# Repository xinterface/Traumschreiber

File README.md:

# Traumschreiber
Repository of the Traumschreiber and all affiliated projects and theses

## Thus far, this includes:

- A collection of theses
- The repos of the two projects concerned with App Design for the Traumschreiber. More information [on EEGDroid](https://github.com/neuroinfo-os/Traumschreiber/blob/master/Theses/App%20Development/RojasCampos_AppRecordStoreManageEEG.pdf) and on [Traumschreiber mobile EEG](https://github.com/neuroinfo-os/Traumschreiber/blob/master/Theses/Event%20Related%20Potentials/Vidal_AuditoryEvokedPotentials.pdf)
- A collection of operation manuals of the hardware components
- In Progress: Streaming implementation
- In Progress: Embedded System and BLE
# Traumschreiber's List (Version 2.8) + (Version EEG_v2_92_X25)
https://docs.google.com/spreadsheets/d/1prQXEEBJC7Lh-TTywT1AkwJn4IeFenbX4uT630RnToc/edit#gid=0

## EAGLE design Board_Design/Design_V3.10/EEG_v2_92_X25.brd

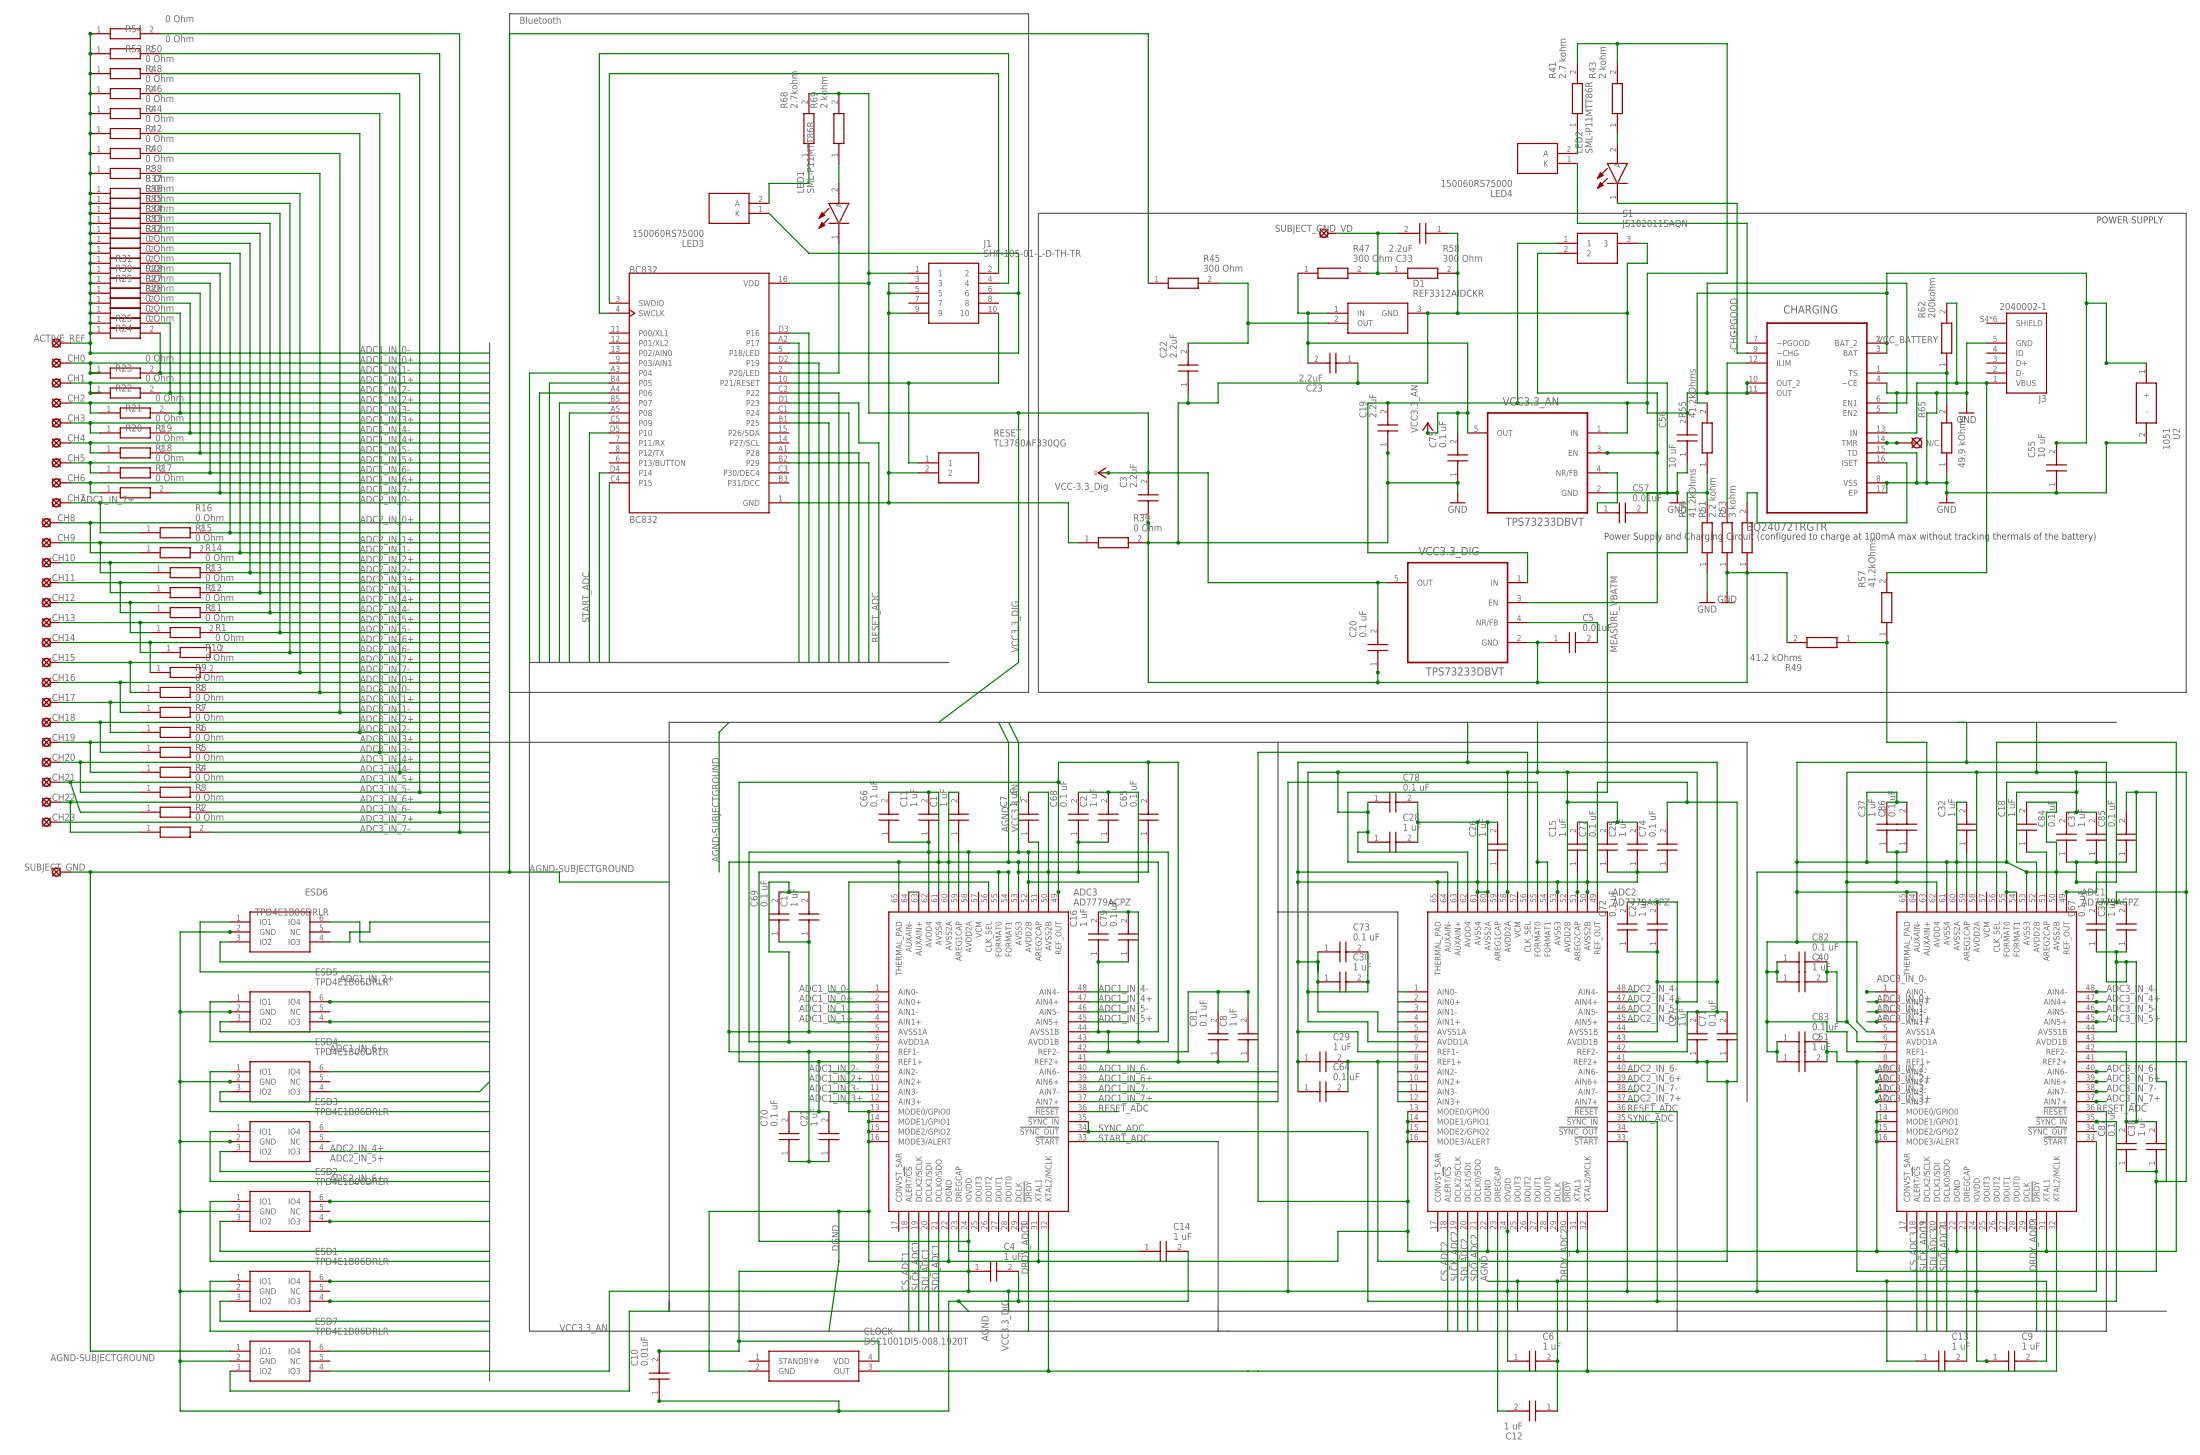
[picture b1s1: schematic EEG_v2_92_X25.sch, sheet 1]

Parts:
ACTIVE_REF: SE11
ADC1, ADC2, ADC3: AD7779ACPZ; QFN50P900X900X80-65N
BC832: BC832; XCVR_BC832
C1, C2, C4, C6, C7, C8, C9, C11, C12, C13, C14, C15, C16, C17, C18, C21, C24, C25, C26, C27, C28, C29, C30, C31, C32, C37, C38, C39, C40, C51: 1 uF; CAPC1005X33N
C3, C19, C22, C23, C33: 2.2uF; CAPC0603X33N
C5, C10, C57: 0.01uF; CAPC0603X33N
C20, C64, C65, C66, C67, C68, C69, C70, C71, C72, C73, C74, C75, C77, C78, C79, C81, C82, C83, C84, C85, C86, C87: 0.1 uF; CAPC0603X33N
C55, C56: 10 uF; CAPC1608X100N
CH0, CH1, CH2, CH3, CH4, CH5, CH6, CH7, CH8, CH9, CH10, CH11, CH12, CH13, CH14, CH15, CH16, CH17, CH18, CH19, CH20, CH21, CH22, CH23: SE11
CHARGING: BQ24072TRGTR; QFN50P300X300X100-17N
CLOCK: DSC1001DI5-008.1920T; DSC1001DI50081920T
D1: REF3312AIDCKR; SOT65P210X110-3N
ESD1, ESD2, ESD3, ESD4, ESD5, ESD6, ESD7: TPD4E1B06DRLR; SOP50P160X60-6N
J1: SHF-105-01-L-D-TH-TR; SHF10501LDTHTR
J3: 2040002-1; TE_2040002-1
LED1, LED2: SML-P11MTT86R; LEDC1006X25N
LED3, LED4: 150060RS75000; LEDC1608X80N
R1, R2, R3, R4, R5, R6, R7, R8, R9, R10, R11, R12, R13, R14, R15, R16, R17, R18, R19, R20, R21, R22, R23, R24, R25, R26, R27, R28, R29, R30, R31, R32, R33, R34, R35, R36, R37, R38, R39, R40, R42, R44, R46, R48, R50, R52, R54: 0 Ohm; RESC1608X55N
R41: 2.7 kohm; RESC0603X26N
R43, R69: 2 kohm; RESC0603X26N
R45, R47, R58: 300 Ohm; RESC0603X26N
R49: 41.2 kOhms; RESC0603X28N
R51: 2.2 kohm; RESC0603X28N
R53: 3 kohm; RESC0603X26N
R55, R56, R57: 41.2kOhms; RESC0603X28N
R62: 200kohm; RESC0603X28N
R65: 49.9 kOhms; RESC0603X28N
R68: 2.7kohm; RESC0603X26N
RESET: TL3780AF330QG
S1: JS102011SAQN
SUBJECT_GND: SE11
SUBJECT_GND_VD: SE11
U2: 1051
VCC3.3_AN, VCC3.3_DIG: TPS73233DBVT; SOT95P280X145-5N

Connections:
-CHG: CHARGING.9 (~CHG), LED2.1 (K)
-PGOOD: CHARGING.7 (~PGOOD), LED4.1 (K)
ADC1_IN_0+: ADC3.2 (AIN0+), CH0.MP, ESD6.4 (IO3), R23.1
ADC1_IN_0-: ACTIVE_REF.MP, ADC3.1 (AIN0-), ESD6.6 (IO4), R24.1, R25.1, R26.1, R27.1, R28.1, R29.1, R30.1, R31.1, R32.1, R33.1, R34.1, R35.1, R36.1, R37.1, R38.1, R40.1, R42.1, R44.1, R46.1, R48.1, R50.1, R52.1, R54.1
ADC1_IN_1+: ADC3.4 (AIN1+), CH1.MP, ESD6.3 (IO2), R22.1
ADC1_IN_1-: ADC3.3 (AIN1-), R23.2, R24.2
ADC1_IN_2+: ADC3.10 (AIN2+), CH2.MP, ESD6.1 (IO1), R21.1
ADC1_IN_2-: ADC3.9 (AIN2-), R22.2, R25.2
ADC1_IN_3+: ADC3.12 (AIN3+), CH3.MP, ESD5.6 (IO4), R20.1
ADC1_IN_3-: ADC3.11 (AIN3-), R21.2, R26.2
ADC1_IN_4+: ADC3.47 (AIN4+), CH4.MP, ESD5.4 (IO3), R19.1
ADC1_IN_4-: ADC3.48 (AIN4-), R20.2, R27.2
ADC1_IN_5+: ADC3.45 (AIN5+), CH5.MP, ESD5.3 (IO2), R18.1
ADC1_IN_5-: ADC3.46 (AIN5-), R19.2, R28.2
ADC1_IN_6+: ADC3.39 (AIN6+), CH6.MP, ESD5.1 (IO1), R17.1
ADC1_IN_6-: ADC3.40 (AIN6-), R18.2, R29.2
ADC1_IN_7+: ADC3.37 (AIN7+), CH7.MP, ESD4.6 (IO4), R16.1
ADC1_IN_7-: ADC3.38 (AIN7-), R17.2, R30.2
ADC2_IN_0+: ADC2.2 (AIN0+), CH8.MP, ESD4.4 (IO3), R15.1
ADC2_IN_0-: ADC2.1 (AIN0-), R16.2, R31.2
ADC2_IN_1+: ADC2.4 (AIN1+), CH9.MP, ESD4.3 (IO2), R14.1
ADC2_IN_1-: ADC2.3 (AIN1-), R15.2, R32.2
ADC2_IN_2+: ADC2.10 (AIN2+), CH10.MP, ESD4.1 (IO1), R13.1
ADC2_IN_2-: ADC2.9 (AIN2-), R14.2, R33.2
ADC2_IN_3+: ADC2.12 (AIN3+), CH11.MP, ESD3.6 (IO4), R12.1
ADC2_IN_3-: ADC2.11 (AIN3-), R13.2, R34.2
ADC2_IN_4+: ADC2.47 (AIN4+), CH12.MP, ESD3.4 (IO3), R11.1
ADC2_IN_4-: ADC2.48 (AIN4-), R12.2, R35.2
ADC2_IN_5+: ADC2.45 (AIN5+), CH13.MP, ESD3.3 (IO2), R1.1
ADC2_IN_5-: ADC2.46 (AIN5-), R11.2, R36.2
ADC2_IN_6+: ADC2.39 (AIN6+), CH14.MP, ESD3.1 (IO1), R10.1
ADC2_IN_6-: ADC2.40 (AIN6-), R1.2, R37.2
ADC2_IN_7+: ADC2.37 (AIN7+), CH15.MP, ESD2.6 (IO4), R9.1
ADC2_IN_7-: ADC2.38 (AIN7-), R10.2, R38.2
ADC3_IN_0+: ADC1.2 (AIN0+), CH16.MP, ESD2.4 (IO3), R8.1
ADC3_IN_0-: ADC1.1 (AIN0-), R9.2, R40.2
ADC3_IN_1+: ADC1.4 (AIN1+), CH17.MP, ESD2.3 (IO2), R7.1
ADC3_IN_1-: ADC1.3 (AIN1-), R8.2, R42.2
ADC3_IN_2+: ADC1.10 (AIN2+), CH18.MP, ESD2.1 (IO1), R6.1
ADC3_IN_2-: ADC1.9 (AIN2-), R7.2, R44.2
ADC3_IN_3+: ADC1.12 (AIN3+), CH19.MP, ESD1.6 (IO4), R5.1
ADC3_IN_3-: ADC1.11 (AIN3-), R6.2, R46.2
ADC3_IN_4+: ADC1.47 (AIN4+), CH20.MP, ESD1.4 (IO3), R4.1
ADC3_IN_4-: ADC1.48 (AIN4-), R5.2, R48.2
ADC3_IN_5+: ADC1.45 (AIN5+), CH21.MP, ESD1.3 (IO2), R3.1
ADC3_IN_5-: ADC1.46 (AIN5-), R4.2, R50.2
ADC3_IN_6+: ADC1.39 (AIN6+), CH22.MP, ESD1.1 (IO1), R2.1
ADC3_IN_6-: ADC1.40 (AIN6-), R3.2, R52.2
ADC3_IN_7+: ADC1.37 (AIN7+), CH23.MP, ESD7.6 (IO4)
ADC3_IN_7-: ADC1.38 (AIN7-), R2.2, R54.2
AGND: ADC1.5 (AVSS1A), ADC1.7 (REF1-), ADC1.42 (REF2-), ADC1.44 (AVSS1B), ADC1.50 (AVSS2B), ADC1.53 (AVSS3), ADC1.60 (AVSS2A), ADC1.61 (AVSS4), ADC1.64 (AUXAIN-), ADC1.65 (THERMAL_PAD), ADC2.5 (AVSS1A), ADC2.7 (REF1-), ADC2.42 (REF2-), ADC2.44 (AVSS1B), ADC2.50 (AVSS2B), ADC2.53 (AVSS3), ADC2.60 (AVSS2A), ADC2.61 (AVSS4), ADC2.64 (AUXAIN-), ADC2.65 (THERMAL_PAD), ADC3.5 (AVSS1A), ADC3.7 (REF1-), ADC3.42 (REF2-), ADC3.44 (AVSS1B), ADC3.50 (AVSS2B), ADC3.53 (AVSS3), ADC3.60 (AVSS2A), ADC3.61 (AVSS4), ADC3.65 (THERMAL_PAD), C1.2, C2.1, C3.1, C4.2, C5.1, C6.2, C7.2, C8.2, C9.2, C10.1, C11.2, C12.1, C13.1, C14.2, C15.2, C16.1, C17.1, C18.2, C19.1, C20.1, C21.1, C22.1, C23.1, C24.1, C25.1, C26.2, C27.2, C28.2, C29.1, C30.1, C31.1, C32.2, C33.1, C37.2, C38.2, C39.1, C40.1, C51.1, C55.1, C56.1, C57.2, C64.1, C65.1, C66.2, C67.1, C68.1, C69.1, C70.1, C71.2, C72.1, C73.1, C74.1, C75.1, C77.1, C78.2, C79.1, C81.2, C82.1, C83.1, C84.1, C85.1, C86.2, C87.2, CHARGING.4 (~CE), CHARGING.5 (EN2), CHARGING.8 (VSS), CHARGING.15 (TD), CHARGING.17 (EP), D1.3 (GND), ESD1.2 (GND), ESD2.2 (GND), ESD3.2 (GND), ESD4.2 (GND), ESD5.2 (GND), ESD6.2 (GND), ESD7.2 (GND), J3.5 (GND), R39.2, R49.2, R51.1, R53.1, R56.1, R58.2, R65.1, S1.3, U2.2 (-), VCC3.3_AN.2 (GND), VCC3.3_DIG.2 (GND)
AGND-SUBJECTGROUND: ESD7.1 (IO1), R45.1, SUBJECT_GND.MP
CS_ADC1: ADC3.18 (ALERT/!CS), BC832.A4 (P06)
CS_ADC2: ADC2.18 (ALERT/!CS), BC832.A5 (P08)
CS_ADC3: ADC1.18 (ALERT/!CS), BC832.C1 (P24)
DGND: ADC1.13 (MODE0/GPIO0), ADC1.14 (MODE1/GPIO1), ADC1.15 (MODE2/GPIO2), ADC1.16 (MODE3/ALERT), ADC1.22 (DGND), ADC1.31 (XTAL1), ADC1.56 (CLK_SEL), ADC2.13 (MODE0/GPIO0), ADC2.14 (MODE1/GPIO1), ADC2.15 (MODE2/GPIO2), ADC2.16 (MODE3/ALERT), ADC2.22 (DGND), ADC2.31 (XTAL1), ADC2.56 (CLK_SEL), ADC3.13 (MODE0/GPIO0), ADC3.14 (MODE1/GPIO1), ADC3.15 (MODE2/GPIO2), ADC3.16 (MODE3/ALERT), ADC3.22 (DGND), ADC3.31 (XTAL1), ADC3.56 (CLK_SEL), BC832.1 (GND), CLOCK.2 (GND), J1.3, J1.5, J1.9, R39.1, RESET.2
DRDY_ADC1: ADC3.30 (!DRDY), BC832.A2 (P17)
DRDY_ADC2: ADC2.30 (!DRDY), BC832.D4 (P14)
DRDY_ADC3: ADC1.30 (!DRDY), BC832.B1 (P25)
MEASURE_VBATM: ADC2.63 (AUXAIN+), R55.1, R56.2
MEASURE_VUSB: ADC1.63 (AUXAIN+), R49.1, R57.1
unnamed: ADC3.59 (AREG1CAP), C1.1
unnamed: ADC2.23 (DREGCAP), C12.2
unnamed: C22.2, D1.2 (OUT), R45.2
unnamed: C5.2, VCC3.3_DIG.4 (NR/FB)
unnamed: BC832.2 (P20/LED), LED1.1 (K)
unnamed: ADC3.63 (AUXAIN+), ADC3.64 (AUXAIN-)
unnamed: ADC3.51 (AREG2CAP), C7.1
unnamed: LED3.2 (A), R68.1
unnamed: LED1.2 (A), R69.1
unnamed: LED4.2 (A), R41.1
unnamed: ADC2.51 (AREG2CAP), C15.1
unnamed: ADC3.23 (DREGCAP), C14.1
unnamed: ADC1.23 (DREGCAP), C13.2
unnamed: LED2.2 (A), R43.1
unnamed: C57.1, VCC3.3_AN.4 (NR/FB)
unnamed: ADC1.59 (AREG1CAP), C32.1
unnamed: ADC2.59 (AREG1CAP), C26.1
unnamed: ADC1.51 (AREG2CAP), C18.1
unnamed: CHARGING.1 (TS), R62.1, R65.2
unnamed: CHARGING.16 (ISET), R53.2
unnamed: CHARGING.12 (ILIM), R51.2
P18/LED: BC832.5 (P18/LED), J1.6, LED3.1 (K)
POWERUP: S1.2, VCC3.3_AN.3 (EN), VCC3.3_DIG.3 (EN)
REF_ADC1: ADC3.8 (REF1+), ADC3.41 (REF2+), ADC3.49 (REF_OUT), C8.1, C21.2, C65.2, C70.2, C81.1
REF_ADC2: ADC2.8 (REF1+), ADC2.41 (REF2+), ADC2.49 (REF_OUT), C27.1, C29.2, C64.2, C71.1, C74.2
REF_ADC3: ADC1.8 (REF1+), ADC1.41 (REF2+), ADC1.49 (REF_OUT), C38.1, C51.2, C83.2, C85.2, C87.1
RESET: BC832.10 (P21/RESET), J1.10, RESET.1
RESET_ADC: ADC1.36 (!RESET), ADC2.36 (!RESET), ADC3.36 (!RESET), BC832.D1 (P23)
SDCLK: BC832.4 (SWCLK), J1.4
SDIO: BC832.3 (SWDIO), J1.2
SDI_ADC1: ADC3.20 (DCLK1/SDI), BC832.C4 (P15)
SDI_ADC2: ADC2.20 (DCLK1/SDI), BC832.B5 (P07)
SDI_ADC3: ADC1.20 (DCLK1/SDI), BC832.A1 (P28)
SDO_ADC1: ADC3.21 (DCLK0/SDO), BC832.D3 (P16)
SDO_ADC2: ADC2.21 (DCLK0/SDO), BC832.B4 (P05)
SDO_ADC3: ADC1.21 (DCLK0/SDO), BC832.B2 (P29)
SHIELD: J3.S4 (SHIELD), J3.S5 (SHIELD), J3.SH1 (SHIELD), J3.SH2 (SHIELD), J3.SH3 (SHIELD), J3.SH4 (SHIELD)
SLCK_ADC1: ADC3.19 (DCLK2/SCLK), BC832.A3 (P04)
SLCK_ADC2: ADC2.19 (DCLK2/SCLK), BC832.D2 (P19)
SLCK_ADC3: ADC1.19 (DCLK2/SCLK), BC832.C2 (P22)
START_ADC: ADC3.33 (!START), BC832.D5 (P10)
SYNC_ADC: ADC1.35 (!SYNC_IN), ADC2.35 (!SYNC_IN), ADC3.34 (!SYNC_OUT), ADC3.35 (!SYNC_IN)
USB_5VOLT+: CHARGING.13 (IN), J3.1 (VBUS), R57.2, R62.2
VCC3.3_AN: ADC1.6 (AVDD1A), ADC1.43 (AVDD1B), ADC1.52 (AVDD2B), ADC1.58 (AVDD2A), ADC1.62 (AVDD4), ADC2.6 (AVDD1A), ADC2.43 (AVDD1B), ADC2.52 (AVDD2B), ADC2.58 (AVDD2A), ADC2.62 (AVDD4), ADC3.6 (AVDD1A), ADC3.43 (AVDD1B), ADC3.52 (AVDD2B), ADC3.58 (AVDD2A), ADC3.62 (AVDD4), C2.2, C11.1, C16.2, C17.2, C23.2, C24.2, C25.2, C28.1, C30.2, C31.2, C37.1, C39.2, C40.2, C66.1, C67.2, C68.2, C69.2, C72.2, C73.2, C75.2, C77.2, C78.1, C79.2, C82.2, C84.2, C86.1, D1.1 (IN), ESD7.3 (IO2), R47.1, VCC3.3_AN.5 (OUT)
VCC3.3_DIG: ADC1.24 (IOVDD), ADC1.33 (!START), ADC1.54 (FORMAT1), ADC1.55 (FORMAT0), ADC2.24 (IOVDD), ADC2.33 (!START), ADC2.54 (FORMAT1), ADC2.55 (FORMAT0), ADC3.24 (IOVDD), ADC3.54 (FORMAT1), ADC3.55 (FORMAT0), BC832.16 (VDD), C3.2, C4.1, C6.1, C9.1, C10.2, C20.2, CLOCK.4 (VDD), ESD7.4 (IO3), J1.1, R68.2, R69.2, VCC3.3_DIG.5 (OUT)
VCC_BATTERY: C55.2, CHARGING.2 (BAT_2), CHARGING.3 (BAT), R55.2, U2.1 (+)
VIRTUAL_GND_PASSIVE: C33.2, R47.2, R58.1, SUBJECT_GND_VD.MP
V_OUT_CHARGER: C19.2, C56.2, CHARGING.6 (EN1), CHARGING.10 (OUT_2), CHARGING.11 (OUT), R41.2, R43.2, S1.1, VCC3.3_AN.1 (IN), VCC3.3_DIG.1 (IN)
XTAL_OUT: ADC1.32 (XTAL2/MCLK), ADC2.32 (XTAL2/MCLK), ADC3.32 (XTAL2/MCLK), CLOCK.3 (OUT)

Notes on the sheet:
Power Supply and Charging Circuit (configured to charge at 100mA max without tracking thermals of the battery)
POWER SUPPLY
Bluetooth

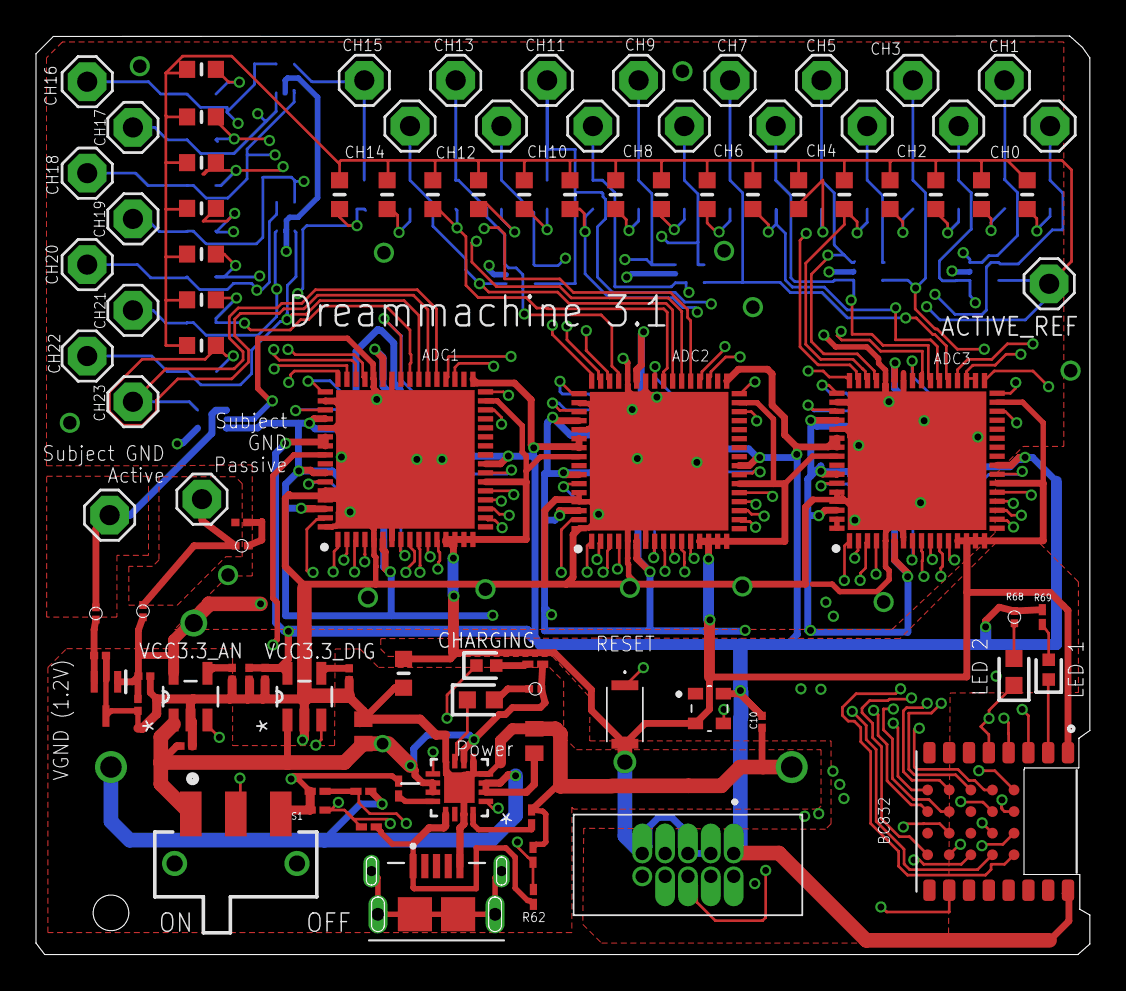
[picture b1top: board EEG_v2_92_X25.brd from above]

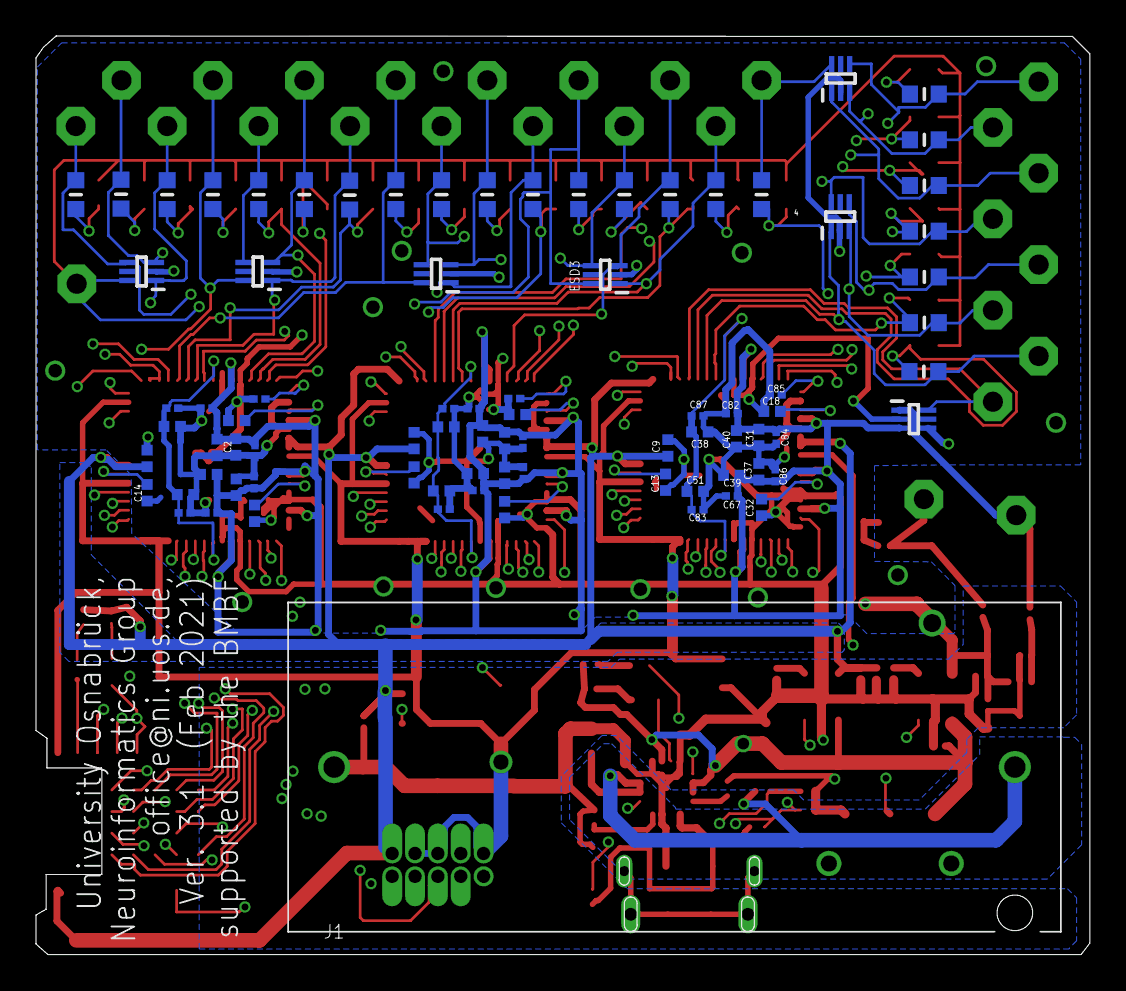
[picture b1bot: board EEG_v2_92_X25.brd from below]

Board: 4 copper layers, 58.5 x 51.0 mm, 177 parts (82 on the bottom side), 110 nets.

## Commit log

2020-03-26 Order Version
2020-03-27 Collection of Bachelor's and Master's theses affiliated with the Traumschreiber
2020-03-27 Changed file name according to convention
2020-03-27 Added beginning of summaries
2020-04-01 Add EEGDroid and Traumschreiber-mobileEEG
2020-04-09 Add sockets test
2020-05-05 Added description of M. Bammel's thesis
2020-05-12 Add working version of streaming listener with storing and plotting of data
2020-05-13 Update working prototype
2020-05-13 Add EEGdroid mod for easier eeg streaming
2020-05-29 Final Version 2.8
    Update V 2.8 - Order Board design
2020-05-31 new version after 2.8
2020-06-09 initial upload
    initial upload of the code that runs on the Traumschreiber
2020-06-09 initial upload
    readme added
2020-06-09 Rewritten streaming_plot.py for jupyter
2020-06-17 Added the app in a new folder with some minor changes for the connection with the new Traumschreiber and the decoding according to the decoding manual, still needs to be included correctly
2020-06-29 changed some parts in the TraumschreiberService.java and in record.java to only work with 6 channels
2020-07-06 Added a constant stream on the diagram to be able to adjust the scales and the adjustion of the y axis
2020-07-10 DataFiles and first analysis
    Contains the FIles evaluating the device noise (of function generator) and Traumschreiber and a first version of the analysis.
2020-07-12 changed the notifyChanges-flag and a part of the connection to receive a stream of data
2020-07-12 fixed receiving of data so that it can be plotted and improved the adjusting of the scale
2020-07-12 Code cleaning
2020-07-13 Added rudimentary GUI for stream control
2020-07-13 env for running jupyter_gui.ipynb
2020-07-14 instable proof of concept
2020-07-16 Canged vendor_prefix
    Prior version does not work for all TS, now, all BT devices are shown in list
2020-07-16 Tried to adapt to new data format
2020-07-17 Files from today's experiment.
    Documentation will follow
2020-07-17 Update EEG-Droid submodule
2020-07-17 Update submodule
2020-07-17 Add some fixes
2020-07-20 Automated and cleaned up plotting
    All csv files are now cleaned uo and plotted automatically. Old datafiles removed and plots included
2020-07-20 Prototype, streaming is slow, algorithm needs improvement
2020-07-21 Collapsed notebook code into one python file
2020-07-22 Update submodule, unify EEGDroid code
2020-07-22 Unify EEGDroid code
2020-07-27 removed jupyter cluuter
2020-07-27 improved dataprocessing during streaming
2020-07-29 Rewrite socket as websocket
2020-07-29 Update submodule, rewrite socket as websocket
2020-07-29 Create Santy check II
2020-08-13 new packet coding, added config characteristic
    date generation changed, can be toggled via config
    gain can be changed via config
    packets contain 6 full channels without compression
2020-08-17 Create V
    SanityCheck V
2020-08-17 SanityCheck5 Analysis
    Added the recent Sanity Check data and cleaned up the prior data a bit
2020-08-20 Create HelloWord.ipynb
    Just a test
2020-08-24 Sanity Check 6 data
2020-08-24 Plots SanityCheck 6
2020-08-24 Experiment Summary
    PDF with the summarized experiments
2020-08-25 cleaned up directory, added support for half sampled/half generated data
2020-09-01 Analysis of jumps I
    Added an analysis of the jumps and cleaned some code. Not a lot though
2020-09-05 changed data flow, fixed notify ack bug, added battery check
    data flow changed to encode on data receive, dropped one ring buffer
    fixed notification acknowledgment bug due to configuration characteristic
    added battery check via config characteristic (sends dummy data for now, due to unresolved spi bug)
2020-09-07 Deleted Files Manually
2020-09-07 Rewritten streaming script and gui as modules
2020-09-07 Added readme
2020-09-09 implemented IIR filtering
    included biquad cascade iir filter from arm_math package
2020-09-10 My work on the app analysis
2020-09-10 2 small bug fixes
    wrong sdk_config file
    iir filter coeffs updated for 250Hz
2020-09-10 bug fix in project file
2020-09-10 fixed Byte order mix-up due to filtering
2020-09-15 implemented sending on 3 characteristics
    also disabled dummy data filtering
2020-09-24 corrected drop count, single characteristic, #nofilter
2020-10-01 added parity check
2020-10-05 Notebooks for analysing lost packages
2020-10-05 Revert "added parity check"
    This reverts commit 9b9c628ff11bc7e8ed673b8f78a771775a401c42.
2020-10-05 Revert "Revert "added parity check""
    This reverts commit 79497ab029f88d69d33ec2d8b5e20f95972fd58e.
2020-10-05 Revert "Revert "Revert "added parity check"""
    This reverts commit c645df2b8641b188dc20eea87e2cd39bc6bd31f9.
2020-10-07 blubb
2020-10-07 added dcpm
    24 channels with 10Bit difference values each
    1 sample (24 channels) is send via 1.5 packages
    sampling at 167Hz
    sending packages at 250Hz
2020-10-07 clean up
2020-10-07 more clean up
2020-10-12 added encoding shift
2020-10-14 Add keyboard-trigger repo for first experiment
2020-10-15 hopefully quick fix to channel numbering
2020-10-17 Update submodules
2020-10-29 added adaptive encoding
2020-11-12 added slowdown debug feature
2020-11-17 change to indication for bitshift updates
2020-11-18 added warm-up and factor safe encoding
2020-11-20 Update version
2020-11-24 Revert commit: 5d17b00
2020-11-24 quick fix 2min30-bug
    switching back to notifications for code-characteristic
    shortening interrupt handling by only sending new packages on AD trigger (dropping the BLE trigger)
2020-11-30 dummy data changed to alternating
2021-01-07 slowing last quickfix and optimising variance calculation
    2min30-bug should be fixed now. buffer capacity calculation was changed for this
    variance calculation now has outsider handling
2021-01-22 bug fix for 2min30 bug
    was caused by a dead lock if ring & BLE buffer were full
2021-01-22 code restructuring/cleaning, added battery monitoring
    program flow was adapted for better interrupt handling
    battery status readout happens at connection event and recording stop (is written in config characteristic)
2021-01-27 encoding-update-always-0 bugfix
2021-02-03 Santycheck_filtering on/off_1Feb2021
2021-02-04 Create 2021-02-03_Santy_check_filtering on,off_signal
2021-02-12 filtering update
    added low pass filter
    notch filter switched to 500Hz (and averaging after)
    coefficients changeable via config char
2021-02-14 intermediate debug version
2021-02-16 added skip tracing in encoding updates
2021-02-16 switching out some filters
2021-02-17 bug fix - only first 8 channels were clean
2021-02-19 added high pass filter and running average calculation
2021-02-23 small bugfix
2021-02-23 added first order high pass filter option
2021-02-23 quick fix
    (take out running average)
2021-03-01 new filter and config structure
2021-03-02 changes on filters, running average, encoding updates
    high pass filtering now @ 167Hz
    running average maybe fixed, still disabled
    encoding updates have priority over regular packages
2021-03-05 fix running average
    (and activated by default, still controllable via config char)
2021-03-08 bugfix encoding updates
2021-03-09 fix package skip count
2021-03-15 Update ad_spi.c
    changed
    4. We change line 410 with spi_estimated_average[n_channel] = spi_estimated_average[n_channel]*spi_enc_estimate_factor_5 + spi_enc_estimate_factor_1*std_5; --->
    spi_estimated_average[n_channel] = spi_estimated_average[n_channel]*spi_enc_estimate_factor_9 + spi_enc_estimate_factor_1*std_5;
    5. We change line 412 with spi_estimated_average[n_channel] = spi_estimated_average[n_channel]*spi_enc_estimate_factor_5 - spi_enc_estimate_factor_1*std_5; --->
    spi_estimated_average[n_channel] = spi_estimated_average[n_channel]*spi_enc_estimate_factor_9 - spi_enc_estimate_factor_1*std_5;
2021-03-15 Update ad_spi.h
    changed
    static float32_t spi_enc_estimate_factor_9 = 0.995;
    static float32_t spi_enc_estimate_factor_1 = 0.005;
    static float32_t spi_enc_estimate_factor_5 = 1.005;
    to have a 1/e decay for 167 samples per second
2021-03-15 bugfix decay rate
2021-03-17 Fix submodule url (ssh->https)
2021-03-22 ordered
    ordered version
2021-03-22 Gordon
2021-03-26 enable larger payload
2021-04-13 widen bitlength support\n\nadded package header
2021-04-19 widen bitlength support
2021-04-21 0.3.3 bug fix - weird data
2021-04-22 0.3.4 bug fix - transmission rate
2021-04-27 Create eegdroid_inspection.py
    This file contains the code I used to create most of the plots that I have shared with the group. BEWARE: contains a fair share of redundancies and spaghetti code.
2021-04-28 Update eegdroid_inspection.py
    Corrected order of processing steps
2021-05-11 0.3.5 filters for 250Hz added
2021-05-18 0.3.6 transmission @ 167/250Hz switchable
2021-05-18 0.3.7 Bits per channel switchable on 3 characteristics
2021-06-09 Removed old code
    Clean up repo by deleting old code (stored locally too)
2021-06-09 Sanity Check Collection
    Added the sanity check summary (june 20 - feb 21) and the results of frequency analysis with MNE (result of CB's lab rotation)
2021-06-14 0.3.8 event length change and battery fix
2021-06-15 0.3.9 another battery fix
